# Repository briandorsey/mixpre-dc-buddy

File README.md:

# mixpre-dc-buddy
DIY MixPre DC power input with SD card access

Just the raw design files for now, more detailed explanation to come. 

# Enclosures
## MixPre-6 (tested with original and II) ##
CAD design (for modification): [OnShape CAD design](https://cad.onshape.com/documents/e7739d92300af53f02275ff7/w/248d08b423cc89cecde0d110/e/cee79aee639158bf5676ad06?renderMode=0&uiState=640cdf0f5e70ba02e0ce10b2)

STL files: [enclosure-6](enclosure-6/)

## MixPre-10 II (only tested with II) ##
CAD design (for modification): [OnShape CAD design](https://cad.onshape.com/documents/4ef6d3906812bf3536cbb43d/w/248db6d6cbcd430f5a7117a5/e/bc656b552057b8b37183c118?renderMode=0&uiState=647d69a6180bea11e23a4cfc)

STL files: [enclosure-10](enclosure-10/)

# parts list

* 3d printed case from CAD above
* PCB from fab files in this repo (I used [Osh Park](https://oshpark.com/shared_projects/2w56M82F) to get them made)
* [CC BEC 2.0 VOLTAGE REGULATOR](https://www.castlecreations.com/en/bec-voltage-regulators-1/cc-bec-2-0-010-0154-00)
* A short DC cable with the right connector for your battery
* nuts and bolts
    * MixPre-6
        * 3x M2.5x16mm hex socket head cap screws
        * 1x M2.5x25mm hex socket head cap screws
        * 5x M2.5 nuts
    * MixPre-10 II
        * 3x M2.5x25mm hex socket head cap screws
        * 3x M2.5 nuts
    * I got an [assortment kit](https://www.amazon.com/gp/product/B07VG889RW/ref=ppx_yo_dt_b_search_asin_title?ie=UTF8&psc=1)

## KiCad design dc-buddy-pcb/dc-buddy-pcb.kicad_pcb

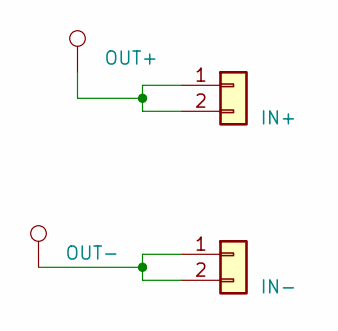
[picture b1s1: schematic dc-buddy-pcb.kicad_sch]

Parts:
OUT_NEG1: OUT-; TestPoint_Pad_4.0x4.0mm
OUT_POS1: OUT+; TestPoint_Pad_4.0x4.0mm
S1: IN+; SolderWire-0.5sqmm_1x02_P4.8mm_D0.9mm_OD2.3mm
S2: IN-; SolderWire-0.5sqmm_1x02_P4.8mm_D0.9mm_OD2.3mm

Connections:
unnamed: OUT_POS1.1, S1.1, S1.2
unnamed: OUT_NEG1.1, S2.1, S2.2

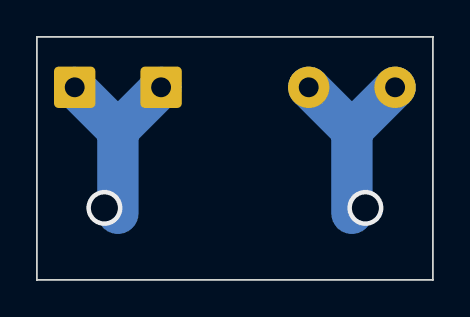
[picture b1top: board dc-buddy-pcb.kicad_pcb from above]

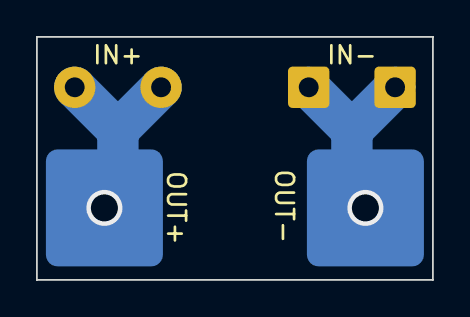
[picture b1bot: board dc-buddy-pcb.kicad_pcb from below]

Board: 2 copper layers, 22.0 x 13.5 mm, 4 parts (4 on the bottom side), 2 nets.

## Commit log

2023-03-11 initial checkin of PCB design
2023-03-11 add resources to README
2023-03-11 added hardware license
2023-03-13 added V1 STL files
2023-06-05 be specific about which MixPre
2023-06-05 initial MixPre-10 ii enclosure STLs
2023-06-05 updated README for MixPre-10 II
2023-06-05 readme tweaks
